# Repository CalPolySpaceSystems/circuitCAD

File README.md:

# Circuit CAD
This repository contains Cal Poly Space Systems' circuit board Design files. 
This includes designed PCBs as well as other resources.
See READMEs in each directory for more information.

# Projects
* UpBoard
* CubeStack
* Flight Recorders
* Peripherals
* Breakouts

# Resources
* Component Libraries
* Design Block/Subassembly Libraries
* CAM jobs for exporting Gerber Files of PCBs

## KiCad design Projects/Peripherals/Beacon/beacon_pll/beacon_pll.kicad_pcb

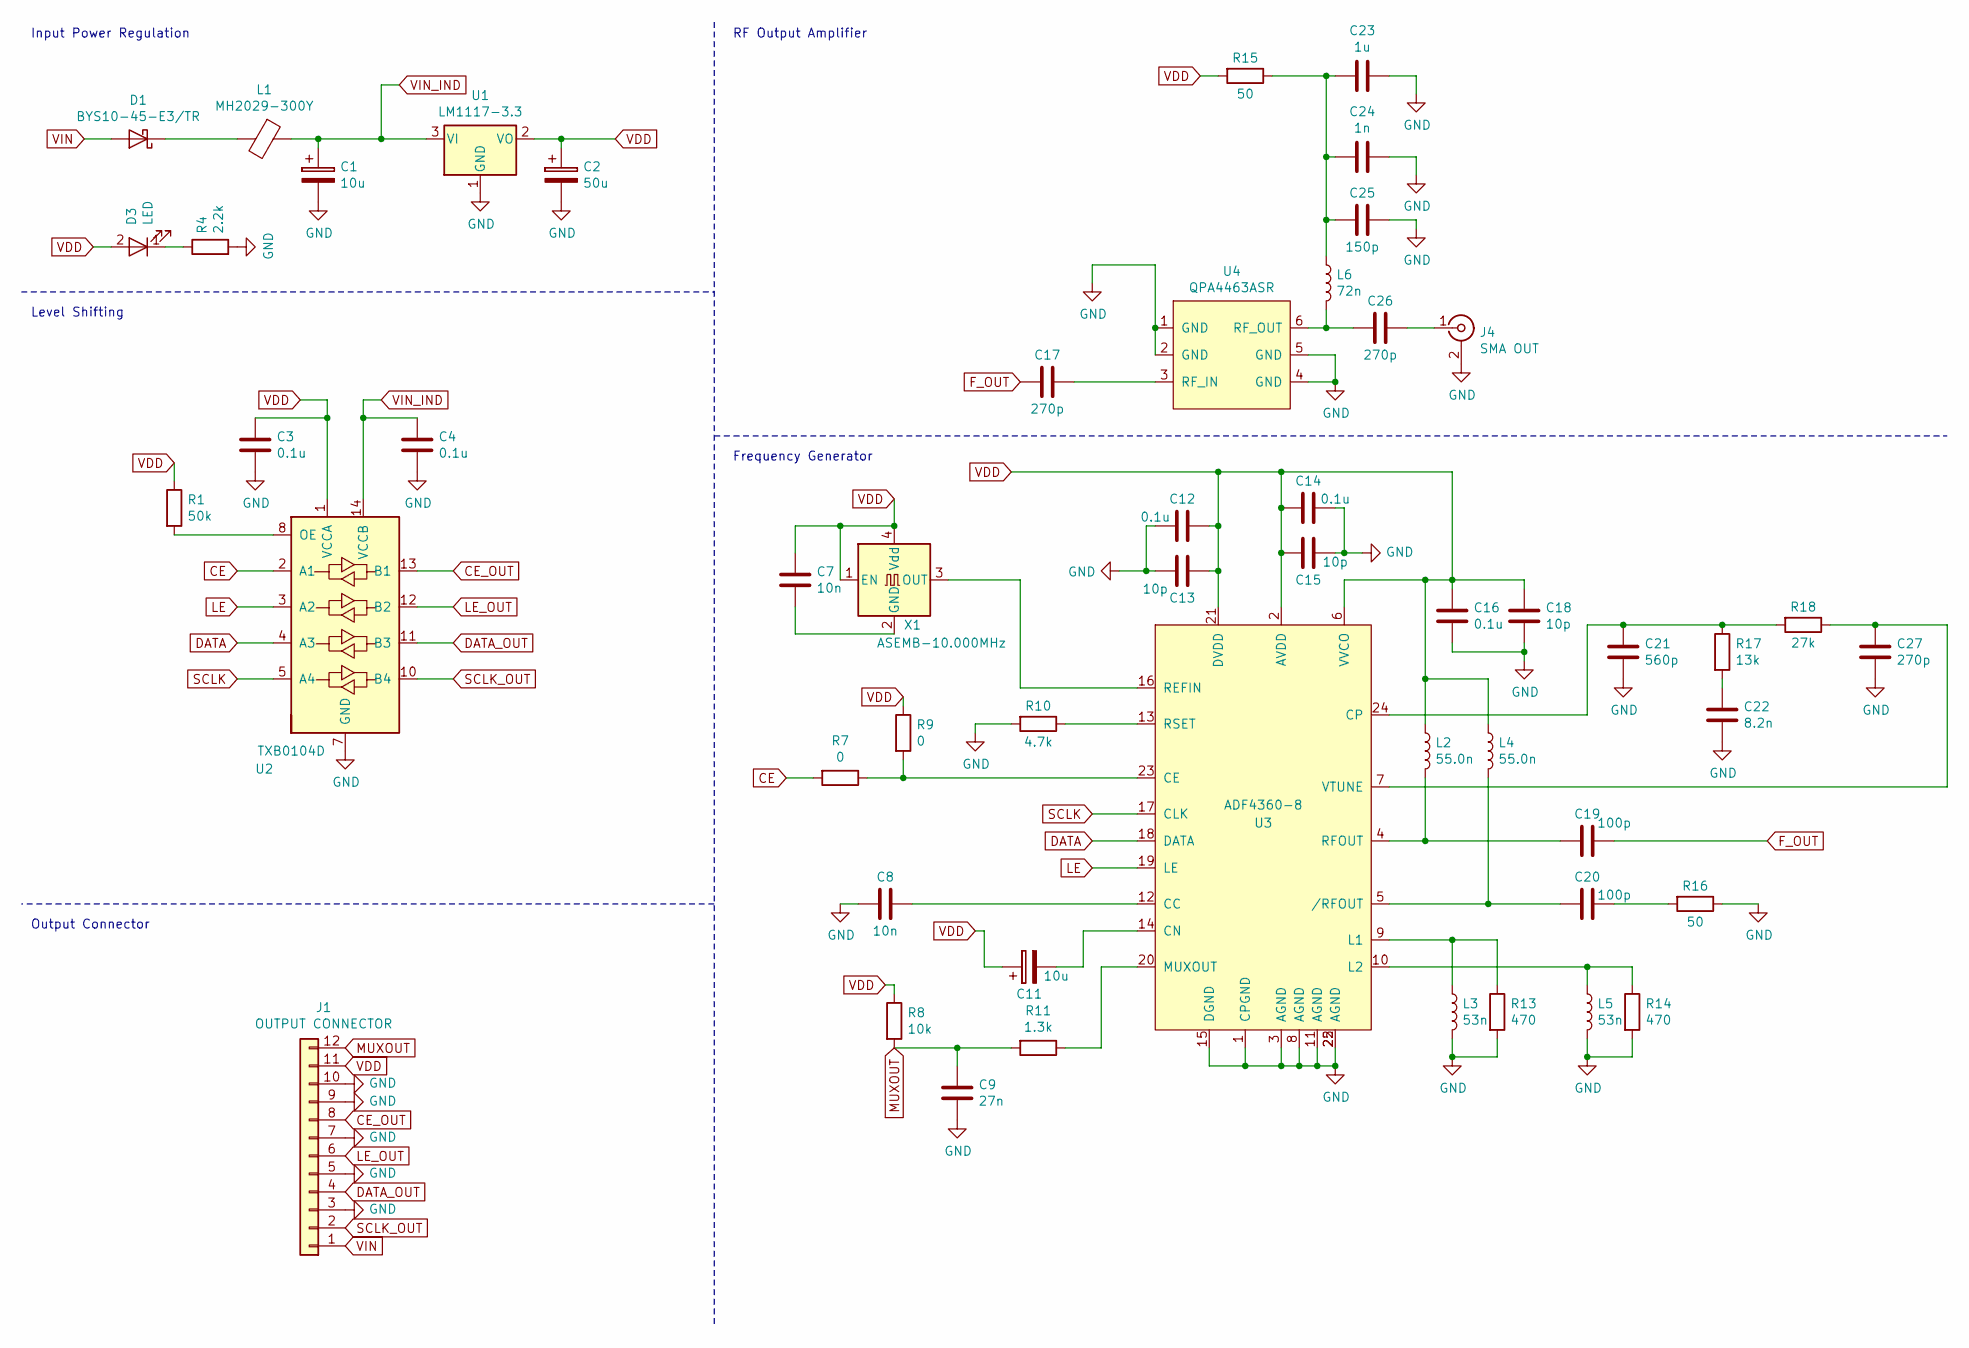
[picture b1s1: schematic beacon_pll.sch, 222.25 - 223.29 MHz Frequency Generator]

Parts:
C1: 10u; C_1206_HandSoldering
C2: 50u; CP_Tantalum_Case-R_EIA-2012-12_Hand
C3, C4, C12, C14, C16: 0.1u; C_0805_HandSoldering
C7, C8: 10n; C_0805_HandSoldering
C9: 27n; C_0805_HandSoldering
C11: 10u; C_0805_HandSoldering
C13, C15, C18: 10p; C_0805_HandSoldering
C17, C26, C27: 270p; C_0805_HandSoldering
C19, C20: 100p; C_0805_HandSoldering
C21: 560p; C_0805_HandSoldering
C22: 8.2n; C_0805_HandSoldering
C23: 1u; C_0805_HandSoldering
C24: 1n; C_0805_HandSoldering
C25: 150p; C_0805_HandSoldering
D1: BYS10-45-E3/TR; D_SMA_Handsoldering
D3: LED; LED_0805_HandSoldering
J1: OUTPUT CONNECTOR; Pin_Header_Straight_2x06_Pitch2.54mm
J4: SMA OUT; Amphenol_RF_SMA_132289
L1: MH2029-300Y; L_0805_HandSoldering
L2, L4: 55.0n; L_0805_HandSoldering
L3, L5: 53n; L_0805_HandSoldering
L6: 72n; L_0805_HandSoldering
R1: 50k; R_0805_HandSoldering
R4: 2.2k; R_0805_HandSoldering
R7, R9: 0; R_0805_HandSoldering
R8: 10k; R_0805_HandSoldering
R10: 4.7k; R_0805_HandSoldering
R11: 1.3k; R_0805_HandSoldering
R13, R14: 470; R_0805_HandSoldering
R15, R16: 50; R_0805_HandSoldering
R17: 13k; R_0805_HandSoldering
R18: 27k; R_0805_HandSoldering
U1: LM1117-3.3; SOT-223
U2: TXB0104D; SOIC-14_3.9x8.7mm_Pitch1.27mm
U3: ADF4360-8; ADF4360-8BCPZRL7
U4: QPA4463ASR; SOT-363_SC-70-6_Handsoldering
X1: ASEMB-10.000MHz; Oscillator_SMD_Abracon_ASE-4pin_3.2x2.5mm

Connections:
CE: R7.2, U2.2 (A1)
CE_OUT: J1.8, U2.13 (B1)
DATA: U2.4 (A3), U3.18 (DATA)
DATA_OUT: J1.4, U2.11 (B3)
F_OUT: C17.2, C19.1
GND: C1.2, C2.2, C3.2, C4.2, C8.2, C9.2, C12.1, C13.1, C14.1, C15.1, C16.2, C18.2, C21.2, C22.2, C23.1, C24.1, C25.1, C27.2, J1.3, J1.5, J1.7, J1.9, J1.10, J4.2 (Ext), L3.2, L5.2, R4.2, R10.2, R13.2, R14.2, R16.1, U1.1 (GND), U2.7 (GND), U3.1 (CPGND), U3.3 (AGND), U3.8 (AGND), U3.11 (AGND), U3.15 (DGND), U3.22 (AGND), U3.25, U4.1 (GND), U4.2 (GND), U4.4 (GND), U4.5 (GND)
LE: U2.3 (A2), U3.19 (LE)
LE_OUT: J1.6, U2.12 (B2)
MUXOUT: C9.1, J1.12, R8.2, R11.2
unnamed: C7.2, X1.2 (GND)
unnamed: C8.1, U3.12 (CC)
unnamed: C11.2, U3.14 (CN)
unnamed: C17.1, U4.3 (RF_IN)
unnamed: C19.2, L2.2, U3.4 (RFOUT)
unnamed: C20.1, R16.2
unnamed: C20.2, L4.2, U3.5 (/RFOUT)
unnamed: C21.1, R17.1, R18.2, U3.24 (CP)
unnamed: C22.1, R17.2
unnamed: C23.2, C24.2, C25.2, L6.1, R15.1
unnamed: C26.1, J4.1 (In)
unnamed: C26.2, L6.2, U4.6 (RF_OUT)
unnamed: C27.1, R18.1, U3.7 (VTUNE)
unnamed: D1.1 (K), L1.2
unnamed: D3.1 (K), R4.1
unnamed: L3.1, R13.1, U3.9 (L1)
unnamed: L5.1, R14.1, U3.10 (L2)
unnamed: R1.2, U2.8 (OE)
unnamed: R7.1, R9.2, U3.23 (CE)
unnamed: R10.1, U3.13 (RSET)
unnamed: R11.1, U3.20 (MUXOUT)
unnamed: U3.16 (REFIN), X1.3 (OUT)
SCLK: U2.5 (A4), U3.17 (CLK)
SCLK_OUT: J1.2, U2.10 (B4)
VDD: C2.1, C3.1, C7.1, C11.1, C12.2, C13.2, C14.2, C15.2, C16.1, C18.1, D3.2 (A), J1.11, L2.1, L4.1, R1.1, R8.1, R9.1, R15.2, U1.2 (VO), U1.4, U2.1 (VCCA), U3.2 (AVDD), U3.6 (VVCO), U3.21 (DVDD), X1.1 (EN), X1.4 (Vdd)
VIN: D1.2 (A), J1.1
VIN_IND: C1.1, C4.1, L1.1, U1.3 (VI), U2.14 (VCCB)

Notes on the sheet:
Input Power Regulation
Level Shifting
Output Connector
RF Output Amplifier
Frequency Generator

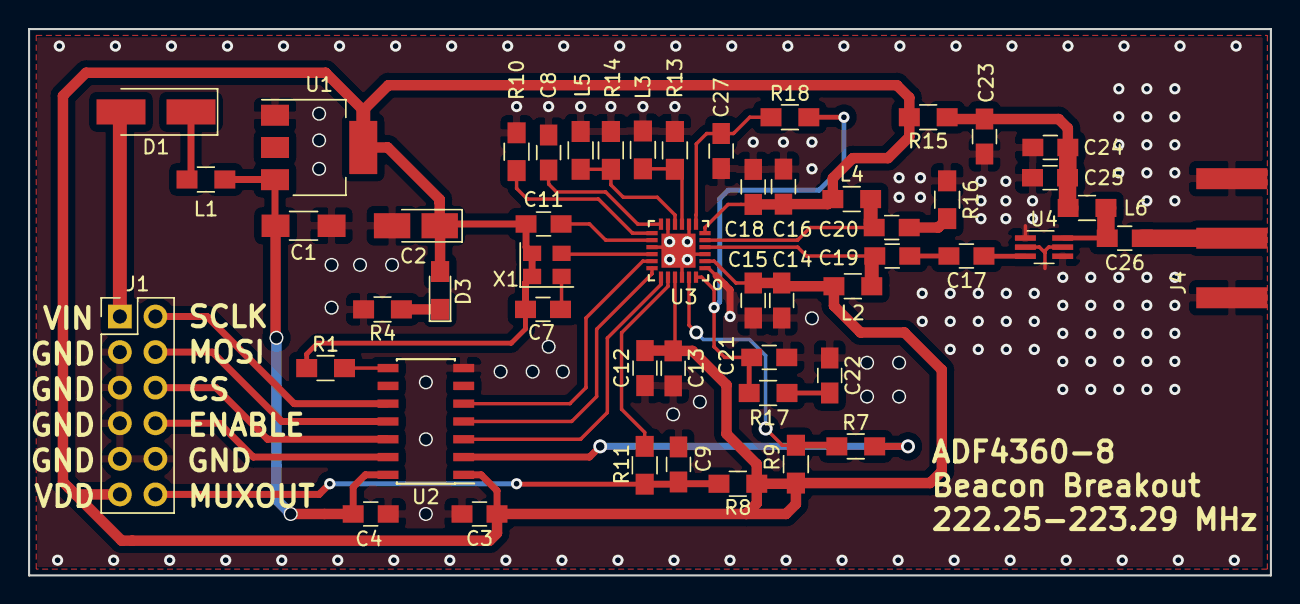
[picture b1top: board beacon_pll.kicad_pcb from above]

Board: 2 copper layers, 88.7 x 39.0 mm, 52 parts (0 on the bottom side), 36 nets.

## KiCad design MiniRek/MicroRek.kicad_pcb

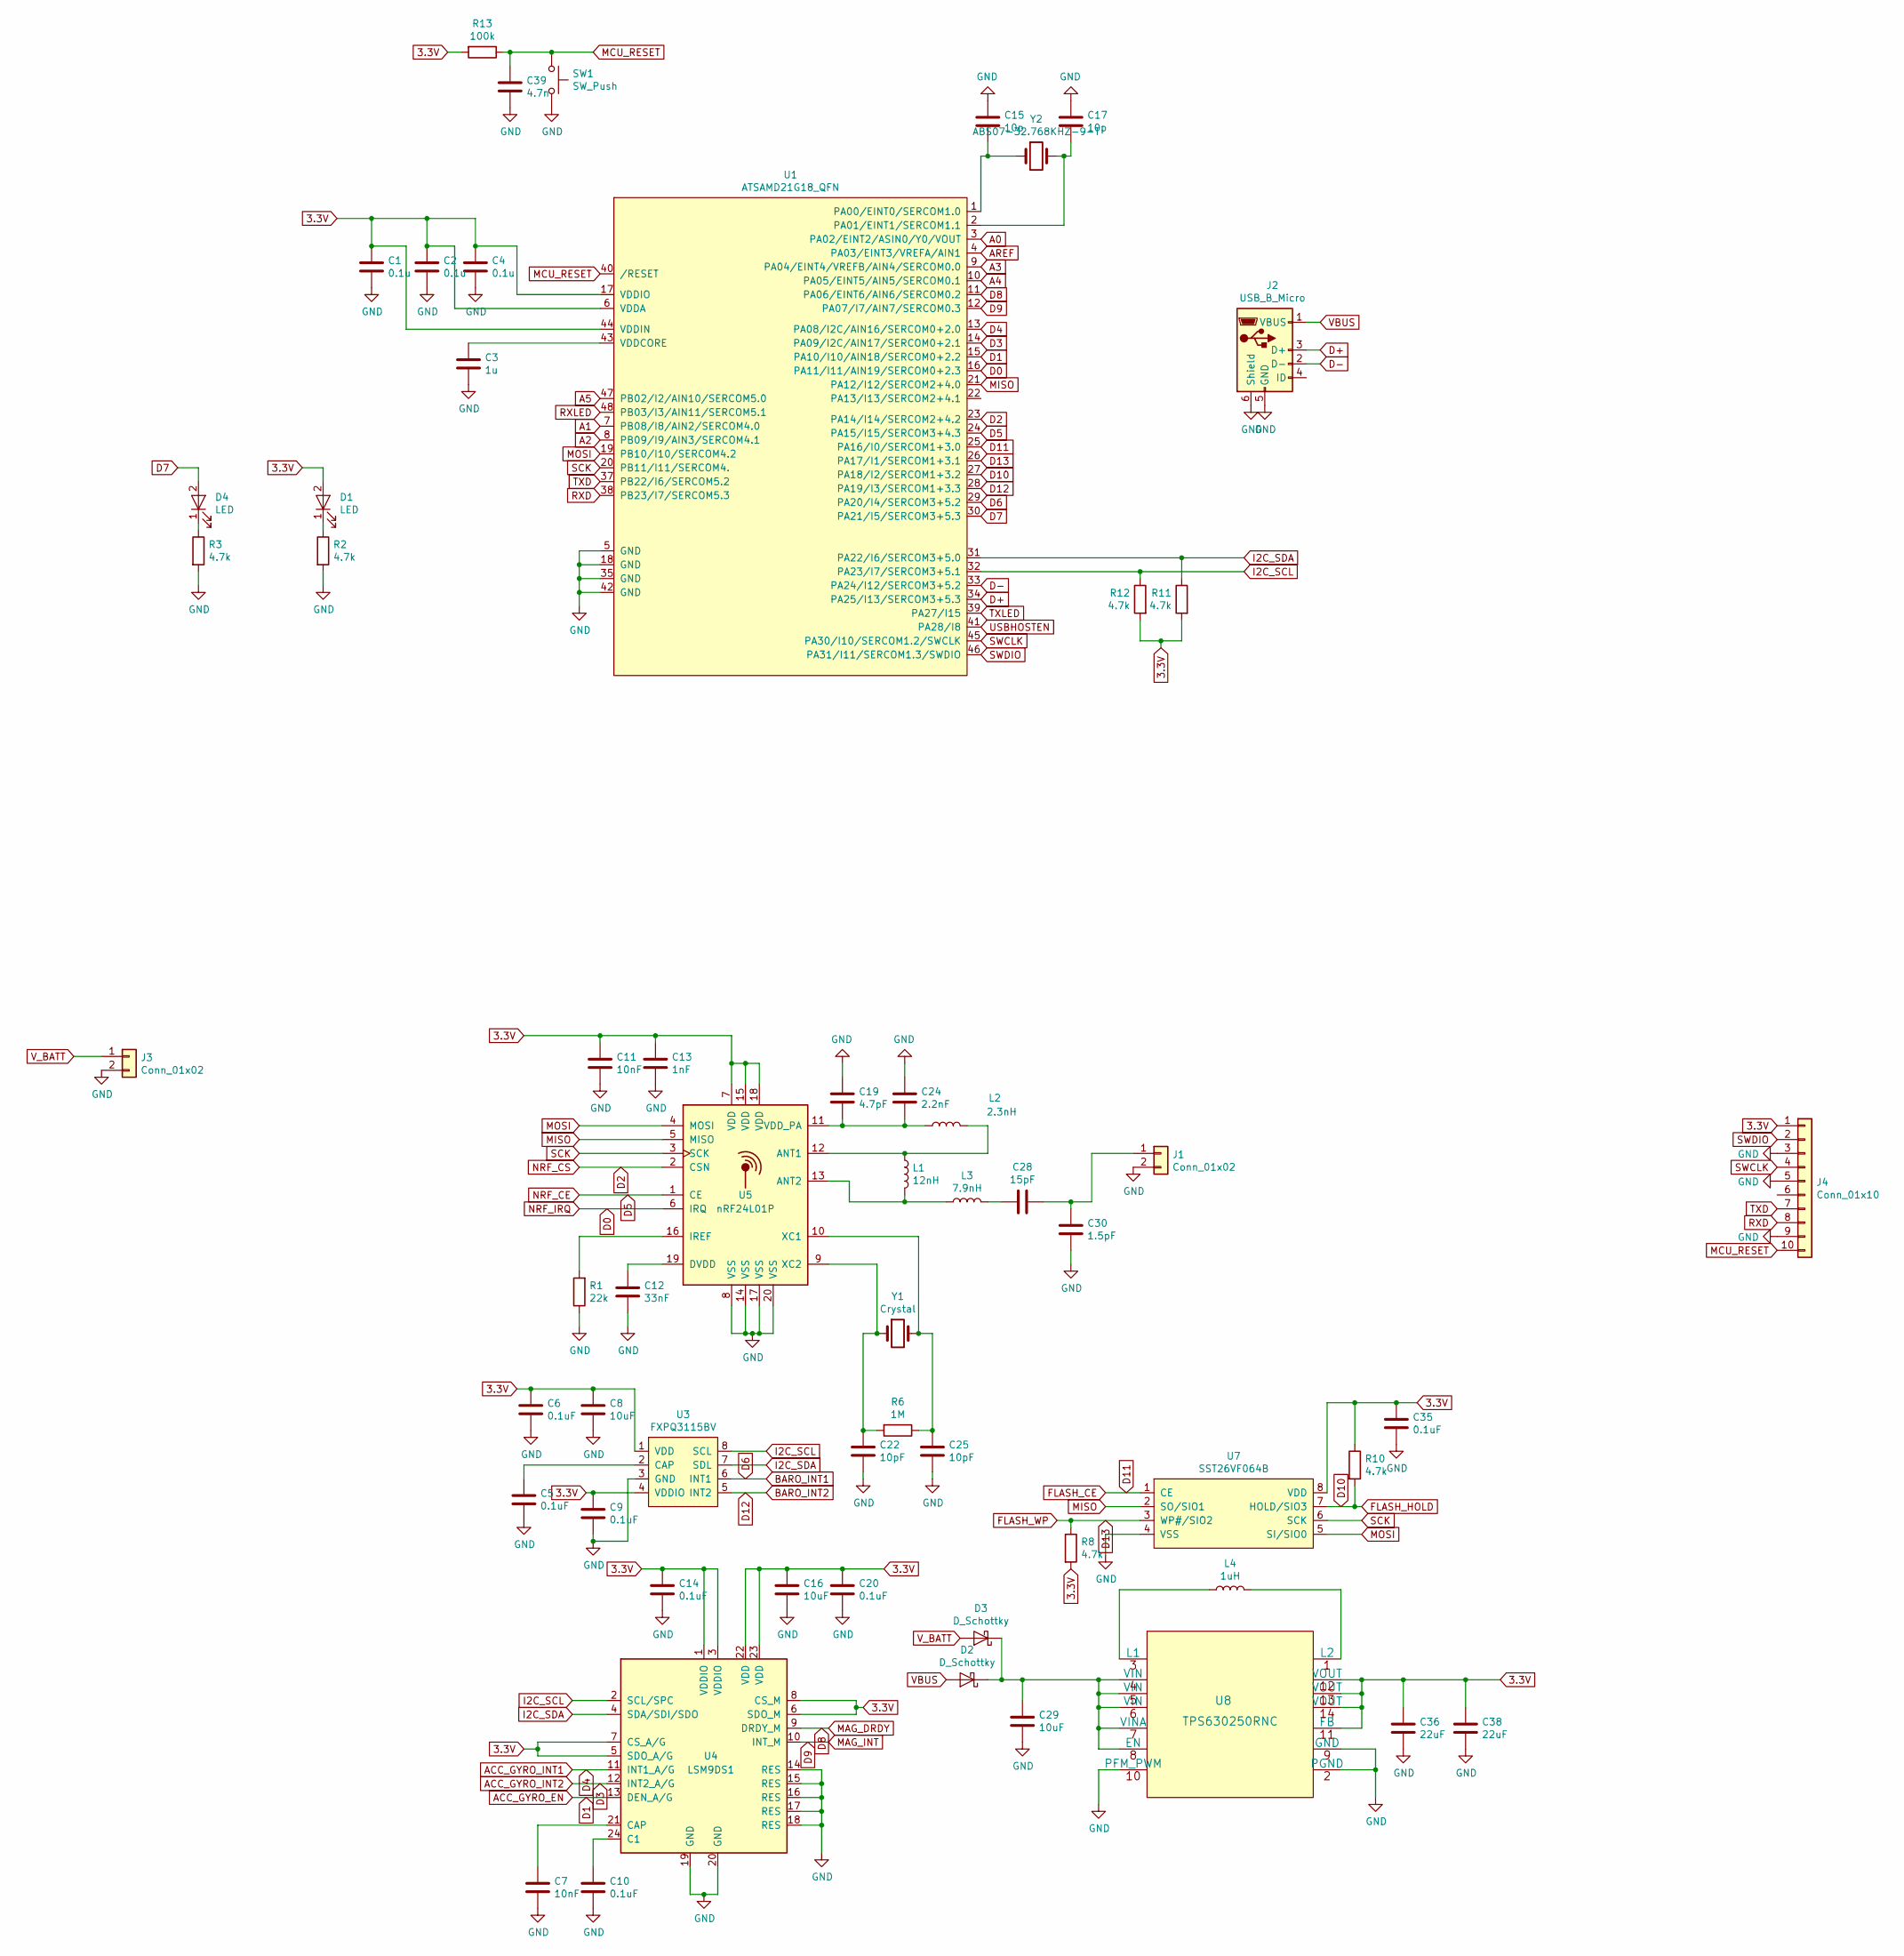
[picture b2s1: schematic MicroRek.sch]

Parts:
C1, C2, C4: 0.1u; C_0603_HandSoldering
C3: 1u; C_0603_HandSoldering
C5, C6, C9, C10, C14, C20, C35: 0.1uF; C_0603_HandSoldering
C7, C11: 10nF; C_0603_HandSoldering
C8, C16, C29: 10uF; C_0805_HandSoldering
C12: 33nF; C_0603_HandSoldering
C13: 1nF; C_0603_HandSoldering
C15, C17: 10p; C_0603_HandSoldering
C19: 4.7pF; C_0603_HandSoldering
C22, C25: 10pF; C_0603_HandSoldering
C24: 2.2nF; C_0603_HandSoldering
C28: 15pF; C_0603_HandSoldering
C30: 1.5pF; C_0603_HandSoldering
C36, C38: 22uF; C_0805_HandSoldering
C39: 4.7n; C_0603_HandSoldering
D1, D4: LED; D_0805
D2: D_Schottky; D_SMA_Handsoldering
D3: D_Schottky; D_1206
J1: Conn_01x02; Amphenol_RF_SMA_132289
J2: USB_B_Micro; USB_Micro-B_Wuerth-629105150521
J3: Conn_01x02; Keystone_1058_1x2032-CoinCell
J4: Conn_01x10; Pin_Header_Straight_2x05_Pitch2.54mm
L1: 12nH; L_0603_HandSoldering
L2: 2.3nH; L_0603_HandSoldering
L3: 7.9nH; L_0603_HandSoldering
L4: 1uH; L_Wuerth_MAPI-4030
R1: 22k; R_0603_HandSoldering
R2, R3, R8, R10, R11, R12: 4.7k; R_0603_HandSoldering
R6: 1M; R_0603_HandSoldering
R13: 100k; R_0603_HandSoldering
SW1: SW_Push; SW_PUSH_6mm
U1: ATSAMD21G18_QFN; QFN-48-1EP_7x7mm_Pitch0.5mm
U3: FXPQ3115BV; LGA-8_3x5mm_Pitch1.25mm
U4: LSM9DS1; LGA-24L_3x3.5mm_Pitch0.43mm
U5: nRF24L01P; QFN-20-1EP_4x4mm_Pitch0.5mm
U7: SST26VF064B; SOIJ-8_5.3x5.3mm_Pitch1.27mm
U8: TPS630250RNC; TPS630250RNCR
Y1: Crystal; Crystal_SMD_Abracon_ABM3-2pin_5.0x3.2mm_HandSoldering
Y2: ABS07-32.768KHZ-9-T

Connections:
3.3V: C1.1, C2.1, C4.1, C6.1, C8.1, C9.1, C11.1, C13.1, C14.1, C16.1, C20.1, C35.1, C36.1, C38.1, D1.2 (A), J4.1, R8.2, R10.1, R11.2, R12.2, R13.2, U1.6 (VDDA), U1.17 (VDDIO), U1.36 (VDDIO2), U1.44 (VDDIN), U3.1 (VDD), U3.4 (VDDIO), U4.1 (VDDIO), U4.3 (VDDIO), U4.5 (SDO_A/G), U4.6 (SDO_M), U4.7 (CS_A/G), U4.8 (CS_M), U4.22 (VDD), U4.23 (VDD), U5.7 (VDD), U5.15 (VDD), U5.18 (VDD), U7.8 (VDD), U8.11 (FB), U8.12 (VOUT), U8.13 (VOUT), U8.14 (VOUT); also elsewhere on the board
A0: U1.3 (PA02/EINT2/ASIN0/Y0/VOUT)
A1: U1.7 (PB08/I8/AIN2/SERCOM4.0)
A2: U1.8 (PB09/I9/AIN3/SERCOM4.1)
A3: U1.9 (PA04/EINT4/VREFB/AIN4/SERCOM0.0)
A4: U1.10 (PA05/EINT5/AIN5/SERCOM0.1)
A5: U1.47 (PB02/I2/AIN10/SERCOM5.0)
ACC_GYRO_EN: U1.15 (PA10/I10/AIN18/SERCOM0+2.2), U4.13 (DEN_A/G)
ACC_GYRO_INT1: U1.13 (PA08/I2C/AIN16/SERCOM0+2.0), U4.11 (INT1_A/G)
ACC_GYRO_INT2: U1.14 (PA09/I2C/AIN17/SERCOM0+2.1), U4.12 (INT2_A/G)
AREF: U1.4 (PA03/EINT3/VREFA/AIN1)
BARO_INT1: U1.29 (PA20/I4/SERCOM3+5.2), U3.6 (INT1)
BARO_INT2: U1.28 (PA19/I3/SERCOM1+3.3), U3.5 (INT2)
D0: U1.16 (PA11/I11/AIN19/SERCOM0+2.3), U5.6 (IRQ)
D2: U1.23 (PA14/I14/SERCOM2+4.2), U5.2 (CSN)
D5: U1.24 (PA15/I15/SERCOM3+4.3), U5.1 (CE)
D7: D4.2 (A), U1.30 (PA21/I5/SERCOM3+5.3)
D8: U1.11 (PA06/EINT6/AIN6/SERCOM0.2), U4.9 (DRDY_M)
D9: U1.12 (PA07/I7/AIN7/SERCOM0.3), U4.10 (INT_M)
D10: R10.2, U1.27 (PA18/I2/SERCOM1+3.2), U7.7 (HOLD/SIO3)
D11: U1.25 (PA16/I0/SERCOM1+3.0), U7.1 (CE)
D13: R8.1, U1.26 (PA17/I1/SERCOM1+3.1), U7.3 (WP#/SIO2)
D+: J2.3 (D+), U1.34 (PA25/I13/SERCOM3+5.3); also elsewhere on the board
D-: J2.2 (D-), U1.33 (PA24/I12/SERCOM3+5.2); also elsewhere on the board
GND: C1.2, C2.2, C3.2, C4.2, C5.2, C6.2, C7.2, C8.2, C9.2, C10.2, C11.2, C12.2, C13.2, C14.2, C15.1, C16.2, C17.1, C19.2, C20.2, C22.2, C24.2, C25.1, C29.2, C30.2, C35.2, C36.2, C38.2, C39.2, J1.2, J2.5 (GND), J2.6 (Shield), J3.2, J4.3, J4.5, J4.9, R1.1, R2.2, R3.2, SW1.2, U1.5 (GND), U1.18 (GND), U1.35 (GND), U1.42 (GND), U1.49, U3.3 (GND), U4.14 (RES), U4.15 (RES), U4.16 (RES), U4.17 (RES), U4.18 (RES), U4.19 (GND), U4.20 (GND), U5.8 (VSS), U5.14 (VSS), U5.17 (VSS), U5.20 (VSS), U5.21, U7.4 (VSS), U8.2 (PGND), U8.9 (GND), U8.10 (PFM_PWM); also elsewhere on the board
I2C_SCL: R12.1, U1.32 (PA23/I7/SERCOM3+5.1), U3.8 (SCL), U4.2 (SCL/SPC)
I2C_SDA: R11.1, U1.31 (PA22/I6/SERCOM3+5.0), U3.7 (SDL), U4.4 (SDA/SDI/SDO)
MCU_RESET: C39.1, J4.10, R13.1, SW1.1, U1.40 (/RESET); also elsewhere on the board
MISO: U1.21 (PA12/I12/SERCOM2+4.0), U5.5 (MISO), U7.2 (SO/SIO1)
MOSI: U1.19 (PB10/I10/SERCOM4.2), U5.4 (MOSI), U7.5 (SI/SIO0)
unnamed: C3.1, U1.43 (VDDCORE)
unnamed: C5.1, U3.2 (CAP)
unnamed: C7.1, U4.21 (CAP)
unnamed: C10.1, U4.24 (C1)
unnamed: C12.1, U5.19 (DVDD)
unnamed: C15.2, U1.1 (PA00/EINT0/SERCOM1.0), Y2.1
unnamed: C17.2, U1.2 (PA01/EINT1/SERCOM1.1), Y2.2
unnamed: C19.1, C24.1, L2.1, U5.11 (VDD_PA)
unnamed: C22.1, R6.2, U5.9 (XC2), Y1.1
unnamed: C25.2, R6.1, U5.10 (XC1), Y1.2
unnamed: C28.1, L3.2
unnamed: C28.2, C30.1, J1.1
unnamed: C29.1, D2.1 (K), D3.1 (K), U8.4 (VIN), U8.5 (VIN), U8.6 (VIN), U8.7 (VINA), U8.8 (EN)
unnamed: D1.1 (K), R2.1
unnamed: D4.1 (K), R3.1
unnamed: L1.1, L2.2, U5.12 (ANT1)
unnamed: L1.2, L3.1, U5.13 (ANT2)
unnamed: L4.1, U8.3 (L1)
unnamed: L4.2, U8.1 (L2)
unnamed: R1.2, U5.16 (IREF)
RXD: J4.8, U1.38 (PB23/I7/SERCOM5.3); also elsewhere on the board
RXLED: U1.48 (PB03/I3/AIN11/SERCOM5.1)
SCK: U1.20 (PB11/I11/SERCOM4.), U5.3 (SCK), U7.6 (SCK)
SWCLK: J4.4, U1.45 (PA30/I10/SERCOM1.2/SWCLK); also elsewhere on the board
SWDIO: J4.2, U1.46 (PA31/I11/SERCOM1.3/SWDIO); also elsewhere on the board
TXD: J4.7, U1.37 (PB22/I6/SERCOM5.2); also elsewhere on the board
TXLED: U1.39 (PA27/I15)
USBHOSTEN: U1.41 (PA28/I8)
VBUS: D2.2 (A), J2.1 (VBUS); also elsewhere on the board
V_BATT: D3.2 (A), J3.1

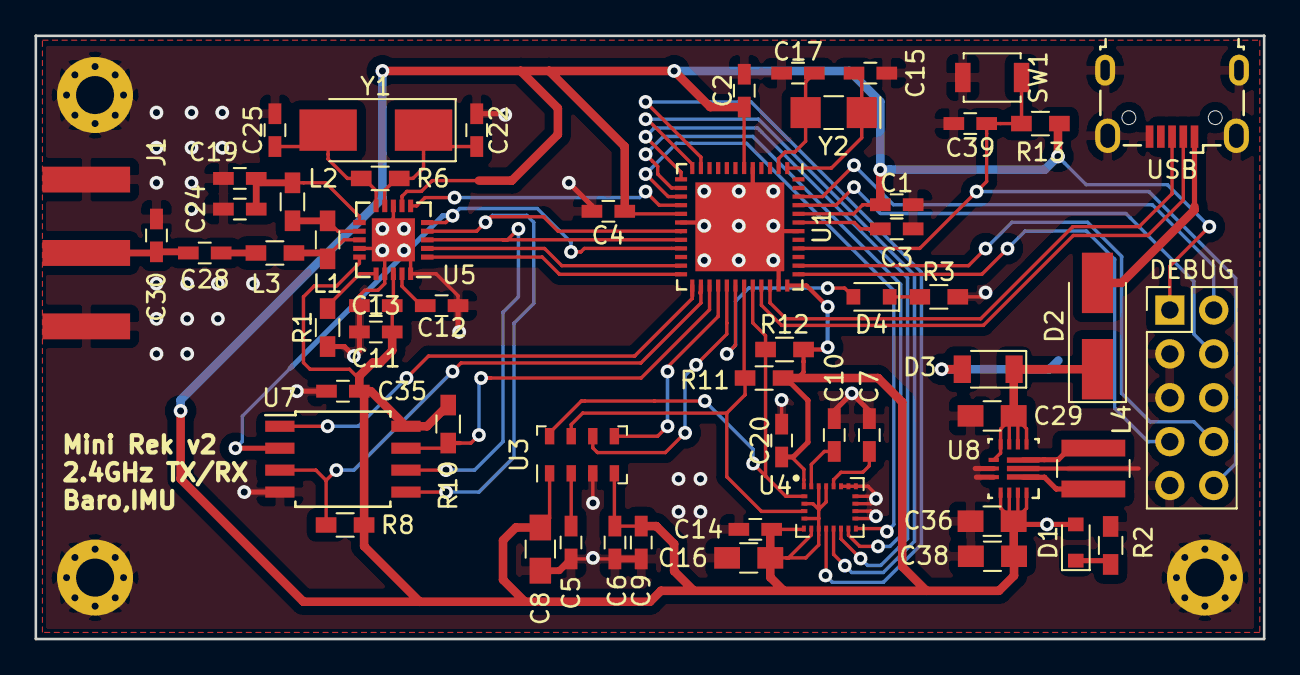
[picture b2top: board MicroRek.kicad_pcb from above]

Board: 2 copper layers, 71.1 x 34.9 mm, 59 parts (1 on the bottom side), 50 nets.

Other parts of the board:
DEBUG: Conn_01x10; Pin_Header_Straight_2x05_Pitch2.54mm
USB: USB_B_Micro; USB_Micro-B_Wuerth-629105150521

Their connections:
3.3V: DEBUG.1; also elsewhere on the board
D+: USB.3; also elsewhere on the board
D-: USB.2; also elsewhere on the board
GND: DEBUG.3, DEBUG.5, DEBUG.9, USB.5, USB.6; also elsewhere on the board
MCU_RESET: DEBUG.10; also elsewhere on the board
RXD: DEBUG.8; also elsewhere on the board
SWCLK: DEBUG.4; also elsewhere on the board
SWDIO: DEBUG.2; also elsewhere on the board
TXD: DEBUG.7; also elsewhere on the board
VBUS: USB.1; also elsewhere on the board

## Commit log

2017-09-24 Committed Josh's IMU to Repository
2017-09-24 Added Patch Circles to highlight areas to be revised
2017-09-29 Revised overly complicated power system
2017-10-10 Simplified power system
2017-10-10 Re-centered Dimensions
2017-10-12 Added CAM file section for UBX
2017-10-12 Finished labeling, removed SPI pull ups
2017-10-12 Fixed Labelling
2017-10-12 Added schematic for UpBoard X in planned configuration
2017-10-21 Initial Commit of the Radio Board
    Radio board PCB and schematic of Rev 1. Datasheets and BOM still to be added.
2017-10-22 Added BOM and PCB GND connections for crystal
2017-10-25 Final Update of Radio Board
    Modified existing silkscreen with name and description on board.
2017-10-26 Add strain gauge board files
    Schematic and most of layout
2017-10-30 First fixes, schematic appearance changes
    Connected D+ line on native USB port. Added title block and reorganized
    schematic to fit on a size C sheet. Revision number is now 1.
2017-10-30 Added R1 PDF Schematic
2017-10-30 Created Readme
2017-10-30 Reorganized Circuit CAD
2017-10-31 Organized power supply into own module
2017-11-03 Sheet Changes
2018-01-13 Added Power Distro
2018-01-13 Added folder
2018-01-30 Added I2C data line
2018-02-10 Created MicroRek Folder
2018-02-10 Revert "Added I2C data line"
    This reverts commit ce24847924fb5b1688f37034ce33982163fc9d56.
2018-02-10 Wired Barometer
2018-02-10 Updated Schematic/Created Board
2018-02-11 Added frame, replaced ATMEGA328P part
2018-02-13 Add git support for CPSS libraries
2018-02-19 Remove EAGLE generated backups
2018-02-19 Add more IC parts
2018-02-19 Pre-Autorouter Commit
2018-02-22 Update R1
2018-02-24 Connected Flash corrctly, changed sheet size
2018-02-26 Finished routing traces, front silkscreen.
2018-02-27 Fixed refdes
2018-02-27 update libraries
2018-02-27 Updated LED drivers
2018-02-28 Added in and routed bjt arrays
2018-02-28 New bjt array
2018-02-28 Fixed naming and silkscreen
2018-03-07 Schemtics and bords
2018-03-07 created and finished upboard radio adapter
2018-03-07 Changed transistors
2018-03-10 Worked on MicroRek Board Still needs lots of work
2018-03-31 Rewiring on Microrek
2018-04-02 Updated MicroRek Board Layout
2018-04-03 updated board
2018-04-05 updated board layout
2018-04-07 LOTS of work on board layout
2018-04-07 Added mini ICSP part
2018-04-09 Added CAM Files for UBXR1 and Adapters
2018-04-12 Added pdf document of UBXR1
2018-04-12 Removed EAGLE backups
2018-04-12 Edit title block
2018-04-21 MicroRek Updates
    Changed inductor package
    Fixed some wiring
    Fixed Crystal wiring (MAYBE)
    Will work more in the morning
2018-05-05 Board Updates
2018-05-08 MicroRek Update
    Added pullup resistors and the mini icsp port
2018-05-15 Added LED's
2018-05-16 small led nd pullup update
2018-05-17 fixed pullup resistors
2018-05-17 Approved Final Schematic
2018-05-19 started new board layout
2018-06-18 Oversized beacon PCB files
    Initial upload of KiCAD design file for a 222.25 to 223.29 MHz single tone transmitter. Uses the ADF4360-8 PLL and has an SPI breakout for control. All parts oversized to 0805 or larger for newbies t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
2018-06-19 Mini Rek Upload
    Like the micro rek but with onboard transmitter. It's a little larger though
2018-06-19 Basic power regulation schematic
2018-06-19 Added PDF outputs and cleaned up schematic
2018-07-15 Work on CubeStack/Stackup
2018-07-15 Added some new parts
2018-07-16 Added intial schematics for pressure board rev 2
2018-08-25 Basic BOM, no parts just footprints and quantities
2018-09-03 PDF of schematic
2018-09-03 Mini Rek Gerbers
2018-09-03 Mini Rek Gerbers Reupload
2018-09-16 First Draft of SAM3X CPU Core
2018-11-10 Modified Libraries, Worked on STM32F3 Core
2018-11-10 Fixed CAD Directories
2018-11-10 Fixed libraries I think
2018-11-11 Routed PWM, GPIO lines
2018-11-14 Added LIS2MDL and LSM6DSL, improved parts
2018-12-20 Removed Feature Drawing examples
2018-12-20 Updated libraries, added EMI shield part
2018-12-20 Completed STM32 Core to be Reviewed
2018-12-20 Schematic and Layout of Sensor Board
    TODO: Fix silkscreen and organize schematic.
2018-12-20 Depricated old Due CPU Core design
2018-12-20 Modified Existing SAM3X CPU for New Bus Pinout
2018-12-21 Added radio board and component libraries
2018-12-22 Added Via Stitching to Perimeter + Bus Pin Numbers
2018-12-22 Organized Silkscreen + Added Bus Pin Numbers
2019-01-02 Created Power Distribution Board with FET Array
    TODO: Change component names
2019-01-02 Update component names
    TODO: Change Resistor/Capacitor names
2019-01-02 Added Connectors and Regulators
2019-01-18 Reorganized CircuitCAD Repo
    Divided into two sections: dependencies and projects. See readmes in each directory for more info
2019-01-18 Put all design blocks and cam jobs into "Resources"
2019-01-18 Created CAM job for ordering from JLCPCB
2019-01-19 Add files via upload
    This folder will contain breakout boards.
2019-01-27 Create Test Code for Arduino Over SPI
2019-01-27 Add files via upload
    This is the EAGLE schematic for the pressure sensor board.
2019-01-27 Rename Projects/Breakouts/Magnetometer/Test Code for Arduino Over SPI to Projects/Breakouts/Test Code for Arduino Over SPI
2019-02-16 Added updated radio GPS board
2019-03-16 Added some part values
2019-03-19 Create SAMD21 CPU.brd
    Finished SAMD21 CPU Design
2019-03-19 Changed C9 package
2019-03-19 Added more vias to SAMD21 Core
2019-07-24 Delete Test Code for Arduino Over SPI
    file unnecessary
2020-01-11 Added Ptap circuit CAD files
2020-01-11 Added PTAP circuit CAD
2020-01-18 Upload of DVR-VTX and PDU2 files

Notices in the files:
parts and their libraries:
Copyright 2016 Accelerated Designs. All rights reserved.
